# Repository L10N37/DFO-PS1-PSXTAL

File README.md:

<html>
<body>

  <h1>PSXTAL DFO - Dual Frequency Oscillator for PS1</h1>

<br>
  
Goes well with my [In Game Reset!](https://github.com/L10N37/PS1-IGR-in-game-reset-PlayStation-Sony-psone)

<br>

<br>
<br>

  <h1>Board Measurements:</h1>
  <p>Approximately 18.5mm * 18.5mm</p>

<br>
<br>

 <h1>PSXTAL DFO V2 Update / Notes</h1>

Options for Reference clock for SI5351-

The 25MHz 3225 reference oscillators come with a few different layouts, the original version 1 board suited JP2, 

JP1: This is for E/D, OE or ST as oscillator pin 1 (Enable Control/ Enable Disable / Output Enable), this ties pin 1 to VCC but often you can leave this pad tri-state / floating, which the board will do by default. 

JP2: This is for oscillators that have pin 1 as a ground, this ties pin 1 to ground. These often work floating (default)

In most cases, you can leave the board as is with pin 1 floating,

I grabbed a reference XTAL from a different bag of 25MHz 3225 XTALS on my last assembly of the board and this shorted out GND to the 3.3v rail. Annoying as hell, the 0603 footprints were way too small and I was installing 0402 components on them instead, this was still difficult. I assumed when I made the version 1 of the board they'd be the same size 0603 footprints I'd used on other boards. They definitely were not. They are now whopping 0805 footprints which should fit 0805, 0603 and 0402 components.

Bypass clock out resistor

JP3 -clock out resistor bypass: You don't need the output resistor for a top mount installatoin if you leave the factory one in place and solder to the old oscillator pads (preferred installation method). For bottom mount installations you will want to leave this open and install the resistor on the DFO board.

A test pad has being added to check the reference clock out with a scope and make sure it's good as the SI5351 pins are tiny and difficult to probe.

  <h1>Components:</h1>
  <ul>
    <li><span class="component">2 * 1k to 10k 0603 resistors:</span> For I2C communication line pullups (SDA/SCL).</li>
    <li><span class="component">1 * Atmega 328P MCU:</span> Clones from Ali are good in my experience. For flashing with the psxtal software that runs the show.</li>
    <li><span class="component">1 * SI5351 clock board, MSOP10 footprint:</span> Ali ones are fine in my experience, though I've read about bad batches. For generating the PS1 GPU clock frequency with glitchless frequency switching.</li>
    <li><span class="component">4 * 100nf (0.1uf) 0603 ceramic capacitors:</span> For bypass capacitors -- 2 for the MCU, 1 for the clock generator IC, 1 for the PLL/Reference oscillator.</li>
    <li><span class="component">1 * 220r 0603 resistor (bypass for top mount):</span> In series on the clock out as per PS1 GPU clock. Originally jumpered (prototype) in case you wanted to top mount / replace the factory GPU oscillator. Instead, we can render that clock useless by removing the on-board 220r resistor on its clock output. I would still personally be removing the factory oscillator completely with hot air.</li>
    <li><span class="component">1 * 25Mhz SMD oscillator:</span> This is used by the SI5351 clock gen IC as a reference clock, please check jumper options</li>
  </ul>

<br>
<br>

  <h1>Flashing</h1>

The board doesn't have any pin headers for any type of ISP flashing. Regular flashing over UART is out of the question as the bare IC's don't come with a bootloader pre-flashed. Instead, you use this (or similar):

This is used in conjunction with an XGecu Pro TL866II Plus to flash the MCU with [this Hex File](https://github.com/L10N37/PSXTAL/blob/main/PSXTAL-DFO/HEX/PSXTAL-DFO.hex) from the original [PSXTAL Repo](https://github.com/L10N37/PSXTAL/tree/main). The original project uses off the shelf parts, installation can be a little messy compared to this custom PCB solution.

<br>
<br>

<h1> Fuse Settings </h1>

<br>
<br>

 <h1> Accuracy </h1>

The project uses the Adafruit SI5351 library, and the math for the clocks was calculated with pen, paper, and a calculator, along with a little trial and error. The original project was installed in many pre-modded systems and tested across many CRTs in my collection on S-video and composite out. Though I've encountered ZERO issues, and neither have my customers - if you can land closer to the exact frequencies, let me know.<br>

 PAL:
 For PU8 / PU18, this frequency divided by 12 equates to your colourburst frequency.<br>
 Actual: 4.43361875 MHz <br>
 This Board: 4.4335 Mhz

<br>
<br>

 NTSC: 
 For PU8 / PU18, this frequency divided by 15 equates to your colourburst frequency.<br>
 Actual: 3.57954 MHz <br>
 This Board: 3.57936Mhz

<br>
<br>

  <h1>Installation</h1>
  <p>It's no different from other DFO's, it uses the same points:</p>
  <ul>
    <li>~3.5v for power</li>
    <li>Ground</li>
    <li>Sense (SO)</li>
    <li>Clock Out</li>
  </ul>
<br>
I would suggest using another install diagram, but buzzing out the points to ones that are more suitable for this boards solder pads. Often you will end up scraping back the green layer on the PCB to create a point.

<br>
<br>

   <h1> Technical PS1 GPU clock Stuff </h1>

  The PU8 and PU18 versions of the Sony Playstation use a GPU oscillator to produce the GPU clocks required for colour generation and screen refresh rate. The CPU clock is generated by a separate oscillator.

  * 53.2034 MHz is for PAL (Europe, Australia, New Zealand and parts of Asia.)
  * 53.693175 MHz is for NTSC (North America, Japan)

  PAL Consoles always start with sense pin high (NTSC mode momentarily) before the BIOS kicks in and initialises the screen. Shortly after power-up, this signal/ pin is pulled to ground and the console will divide the GPU clock by 12. This gives you the 4.43Mhz you need to produce PAL colours on your set when using S-Video or Composite output. The problem when running an NTSC game on these consoles, is that the console will divide the GPU clock by 15 in NTSC mode. Using an approximation of  53.2 / 15, this gives you about a 3.54Mhz subcarrier signal. This isn't a valid clock signal and you get a black and white picture.
<br>
<br>
<h2> Old School Fix  </h2>
<br>  

  The 'old-school' fix to get colour was to take the video encoders sub carrier input pin, lift it off the board and feed it a perma-4.43Mhz PAL colour sub-carrier clock signal. This way, regardless of the PS1 being in PAL or NTSC Mode, you would still have the PAL sub carrier required to give you a colour picture. the *problem* with this is that, these days - scalers are very popular devices. Now when the console is in NTSC mode and using this 'old-school' sub carrier modification, we get around a 59.24hz refresh rate. The actual 60hz refresh rate should be 59.94Hz. This discrepancy causes frame drops, stuttering and other issues when combining this fix with a scaler. For CRT's, the small discepancy is a non issue. When using RGB, you'll get colour regardless (no fix required), but the small clock discrepancies are still prevelant.

<br>
<br>
<h2> Modern Fix  </h2>
<br>

Nowadays, we can use nifty modern ICs to simply toggle between the 2 GPU clocks. This gives you 'true' NTSC and PAL modes with their respective 'true' subcarrier clocks. The console is now truly multi-region. There are only 2 or 3 NTSC games that won't work on a PAL console (some have patches) due to the crafty developers adding code to detect the mechacon in the console! Unfortunately, PAL consoles still have PAL mechacons and NTSC consoles have NTSC mechacons. They only seem to check for NTSC/PAL and nothing in the BIOS, as the US games mentioned work on JP consoles.

<br>
<br>
<h2> What about the later models? PU20, PU22, PU23 and PM41 revisions? </h2>
<br>

Sony switched from using oscillators to produce the clocks, to instead, using a clock generator IC with PLL reference clock. See here.

A PCB will be designed in the future to cover the Sub-Carrier clock outputs, along with the GPU clock outputs. I do have [PSXTAL 3FO](https://github.com/L10N37/PSXTAL/blob/main/PU22%2B/PU23ClockGen.png), which outputs a very slightly overclocked CPU, along with GPU clocks and Sub-Carrier clocks that toggle on sense. I didn't have a 100% success rate with PAL mode on this project. It was probably because of using a different PLL to produce the GPU than the Sub carrier in PAL mode. It does work, but some sets will be black and white in PAL mode. It needs a re-visit.

   <h1>Notes and support</h1>

Since losing some of my KiCad files and not being able to make modifications to old projects, I choose to share them openly. It benefits me, and at the same time, if anyone is interested, they can jump in and do their own thing. I don't care if you make these and sell them for profit. Do whatever you want. I am happy to assist if you have any questions. This guide is not for beginners. Note that the resistors and capacitors have no wiggle room and are not easy to hand solder. A hot air station will come in handy.

  [License: Creative Commons Attribution-ShareAlike (CC BY-SA)](https://creativecommons.org/licenses/by-sa/4.0/)

</body>
</html>

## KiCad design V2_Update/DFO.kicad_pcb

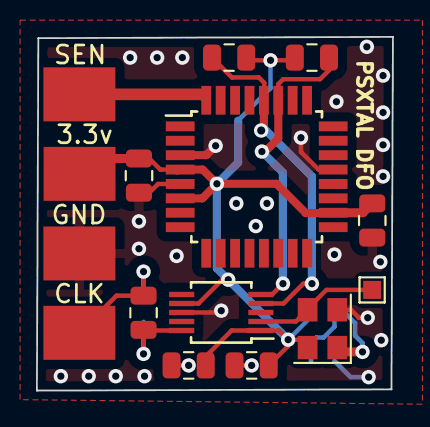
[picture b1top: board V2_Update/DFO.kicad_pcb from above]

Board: 2 copper layers, 19.8 x 19.6 mm, 3 parts (0 on the bottom side), 5 nets.

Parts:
U1: Si5351A-B-GT; MSOP-10_3x3mm_P0.5mm
U2: ATmega328-A; TQFP-32_7x7mm_P0.8mm
X1: ASE-25MHz; Oscillator_SMD_Abracon_ASE-4Pin_3.2x2.5mm

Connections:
+3.3V: U1.1 (VDD), U1.7 (VDDO), U2.4 (VCC), U2.6 (VCC), U2.18 (AVCC), X1.4 (Vdd)
GND: U1.8 (GND), U2.3 (GND), U2.5 (GND), U2.21 (GND), X1.2 (GND)
REF_CLK_OUT: U1.2 (XA), X1.3 (OUT)
i2c-SCL: U1.4 (SCL), U2.28 (PC5)
i2c-SDA: U1.5 (SDA), U2.27 (PC4)

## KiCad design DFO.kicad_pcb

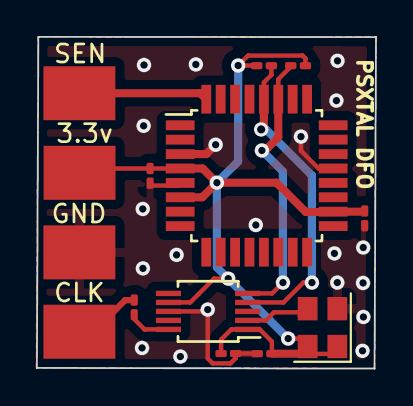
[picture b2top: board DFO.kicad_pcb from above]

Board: 2 copper layers, 18.8 x 18.4 mm, 10 parts (0 on the bottom side), 6 nets.

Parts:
C1, C2, C3, C6: 100nf; C_0201_0603Metric_Pad0.64x0.40mm_HandSolder
R1, R2: 10k; R_0201_0603Metric_Pad0.64x0.40mm_HandSolder
R3: 220r; R_0201_0603Metric_Pad0.64x0.40mm_HandSolder
U1: Si5351A-B-GT; MSOP-10_3x3mm_P0.5mm
U2: ATmega328-A; TQFP-32_7x7mm_P0.8mm
X1: ASE-25MHz; Oscillator_SMD_Abracon_ASE-4Pin_3.2x2.5mm

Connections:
+3.3V: C1.1, C2.1, C3.1, C6.1, R1.1, R2.1, U1.1 (VDD), U1.7 (VDDO), U2.4 (VCC), U2.6 (VCC), U2.18 (AVCC), X1.1 (EN), X1.4 (Vdd)
GND: C1.2, C2.2, C3.2, C6.2, U1.8 (GND), U2.3 (GND), U2.5 (GND), U2.21 (GND), X1.2 (GND)
unnamed: R3.1, R3.2, U1.CLKOUT (CLK0)
unnamed: U1.2 (XA), X1.3 (OUT)
i2c-SCL: R1.2, U1.4 (SCL), U2.28 (PC5)
i2c-SDA: R2.2, U1.5 (SDA), U2.27 (PC4)

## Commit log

2023-05-18 Create temp
2023-05-18 ADD GERBER FILES
2023-05-18 Update README.md installation section
2023-05-18 Update README, add IGR link
2023-05-20 add kicad stuff
2023-05-20 update files
2023-05-20 update files:
2024-01-30 Add V2 Update
2024-01-30 v2 update
2024-01-30 fixed 2 GND points PCB
2024-01-30 update manufacturer zip file
2024-02-04 Restructure
